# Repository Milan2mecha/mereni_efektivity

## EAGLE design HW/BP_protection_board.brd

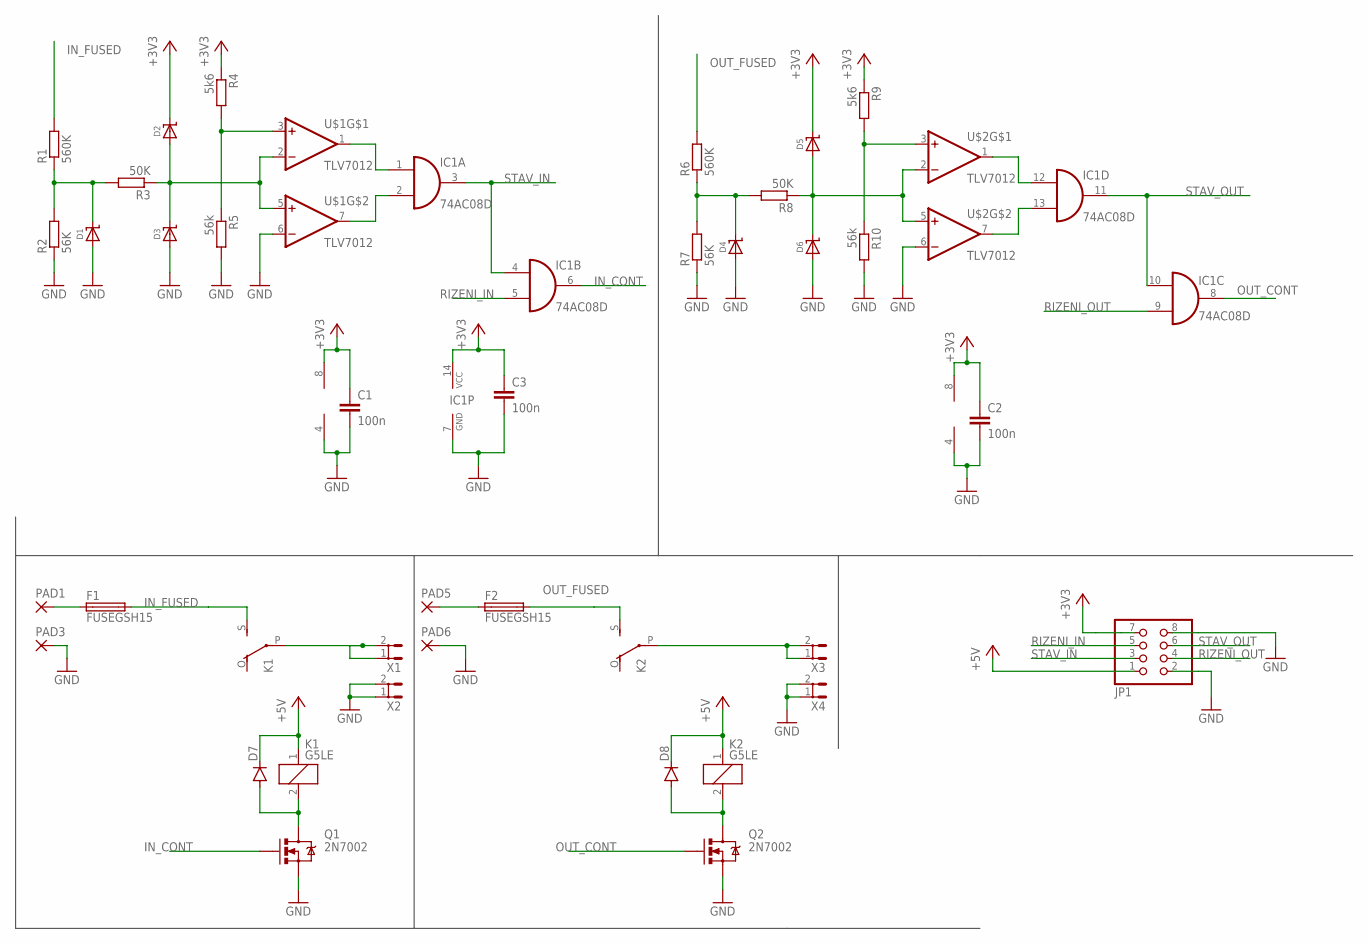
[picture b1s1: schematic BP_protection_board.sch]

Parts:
C1, C2, C3: 100n; C0805
D1, D2, D3, D4, D5, D6: DIODE-SCHOTTKYSOD-123; SOD-123
D7, D8: DIODE-MELF-MLL41; MELF-MLL41
F1, F2: FUSEGSH15; GSH15
IC1: 74AC08D; SO14
JP1: PINHD-2X4; 2X04
K1, K2: G5LE
PAD1, PAD3, PAD5, PAD6: 2,54/1,0
Q1, Q2: 2N7002; SOT323
R1, R6: 560K; R0805
R2, R7: 56K; R0805
R3, R8: 50K; R0805
R4, R9: 5k6; R0805
R5, R10: 56k; R0805
U$1, U$2: TLV7012; SOT-23-THIN
X1, X2, X3, X4: ST6,3

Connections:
+3V3: C1.1, C2.1, C3.1, D2.C, D5.C, IC1.14 (VCC), JP1.7, R4.1, R9.1, U$1.8 (V+), U$2.8 (V+)
+5V: D7.C, D8.C, JP1.1, K1.1, K2.1
GND: C1.2, C2.2, C3.2, D1.A, D3.A, D4.A, D6.A, IC1.7 (GND), JP1.2, JP1.8, PAD3.1, PAD6.1, Q1.2 (S), Q2.2 (S), R2.1, R5.2, R7.1, R10.2, U$1.4 (V-), U$1.6 (-IN), U$2.4 (V-), U$2.6 (-IN), X2.1, X2.2, X4.1, X4.2
IN_CONT: IC1.6 (O), Q1.1 (G)
IN_FUSED: F1.2, K1.S, R1.2
unnamed: D1.C, R1.1, R2.2, R3.2
unnamed: D2.A, D3.C, R3.1, U$1.2 (-IN), U$1.5 (+IN)
unnamed: R4.2, R5.1, U$1.3 (+IN)
unnamed: D4.C, R6.1, R7.2, R8.2
unnamed: F1.1, PAD1.1
unnamed: D5.A, D6.C, R8.1, U$2.2 (-IN), U$2.5 (+IN)
unnamed: R9.2, R10.1, U$2.3 (+IN)
unnamed: K1.P, X1.1, X1.2
unnamed: K2.P, X3.1, X3.2
unnamed: D8.A, K2.2, Q2.3 (D)
unnamed: D7.A, K1.2, Q1.3 (D)
unnamed: IC1.1 (I0), U$1.1 (OUT)
unnamed: IC1.2 (I1), U$1.7 (OUT)
unnamed: F2.1, PAD5.1
unnamed: IC1.12 (I0), U$2.1 (OUT)
unnamed: IC1.13 (I1), U$2.7 (OUT)
OUT_CONT: IC1.8 (O), Q2.1 (G)
OUT_FUSED: F2.2, K2.S, R6.2
RIZENI_IN: IC1.5 (I1), JP1.5
RIZENI_OUT: IC1.9 (I0), JP1.4
STAV_IN: IC1.3 (O), IC1.4 (I0), JP1.3
STAV_OUT: IC1.10 (I1), IC1.11 (O), JP1.6

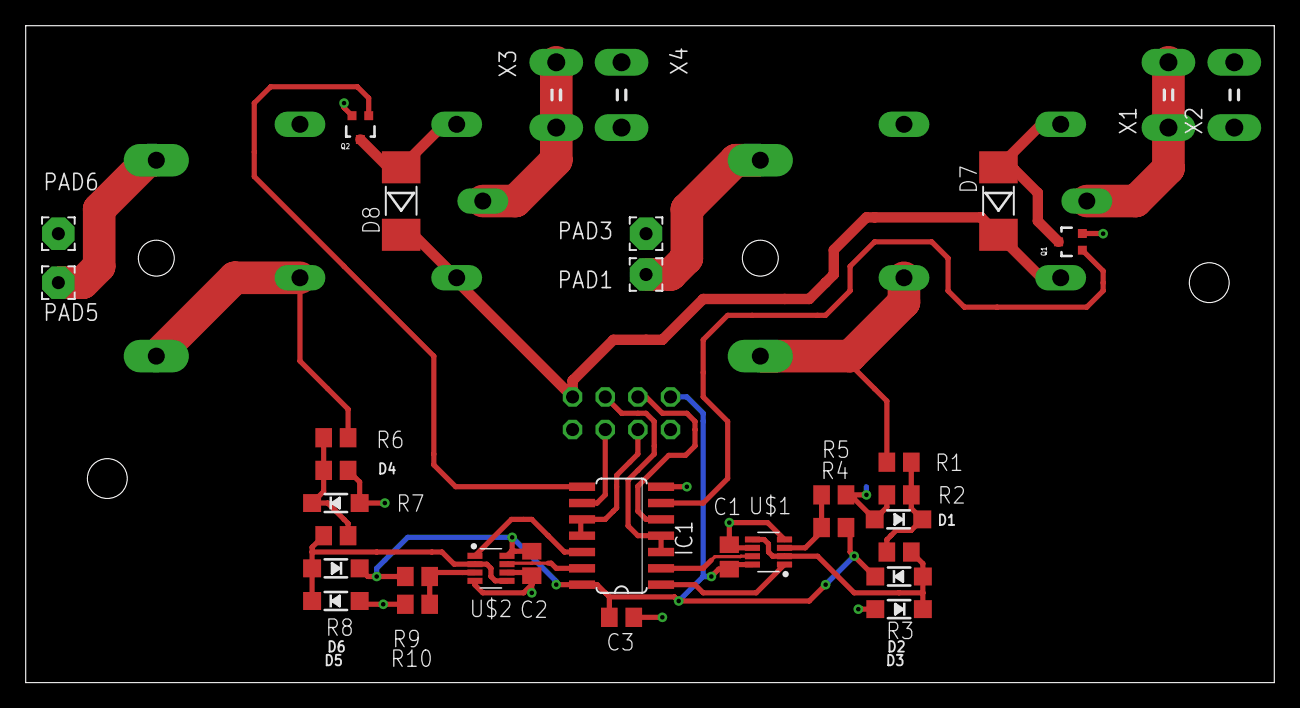
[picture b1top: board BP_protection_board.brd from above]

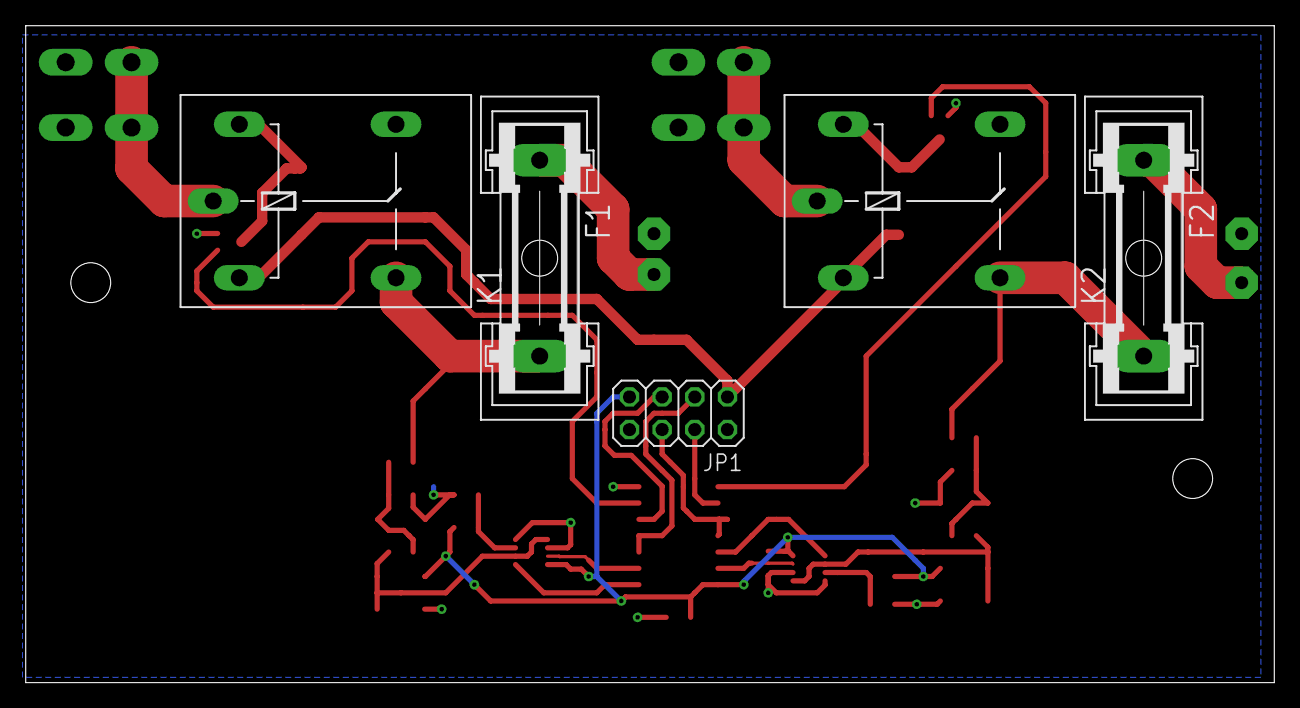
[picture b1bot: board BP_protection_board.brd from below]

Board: 2 copper layers, 97.1 x 51.1 mm, 39 parts (5 on the bottom side), 27 nets.

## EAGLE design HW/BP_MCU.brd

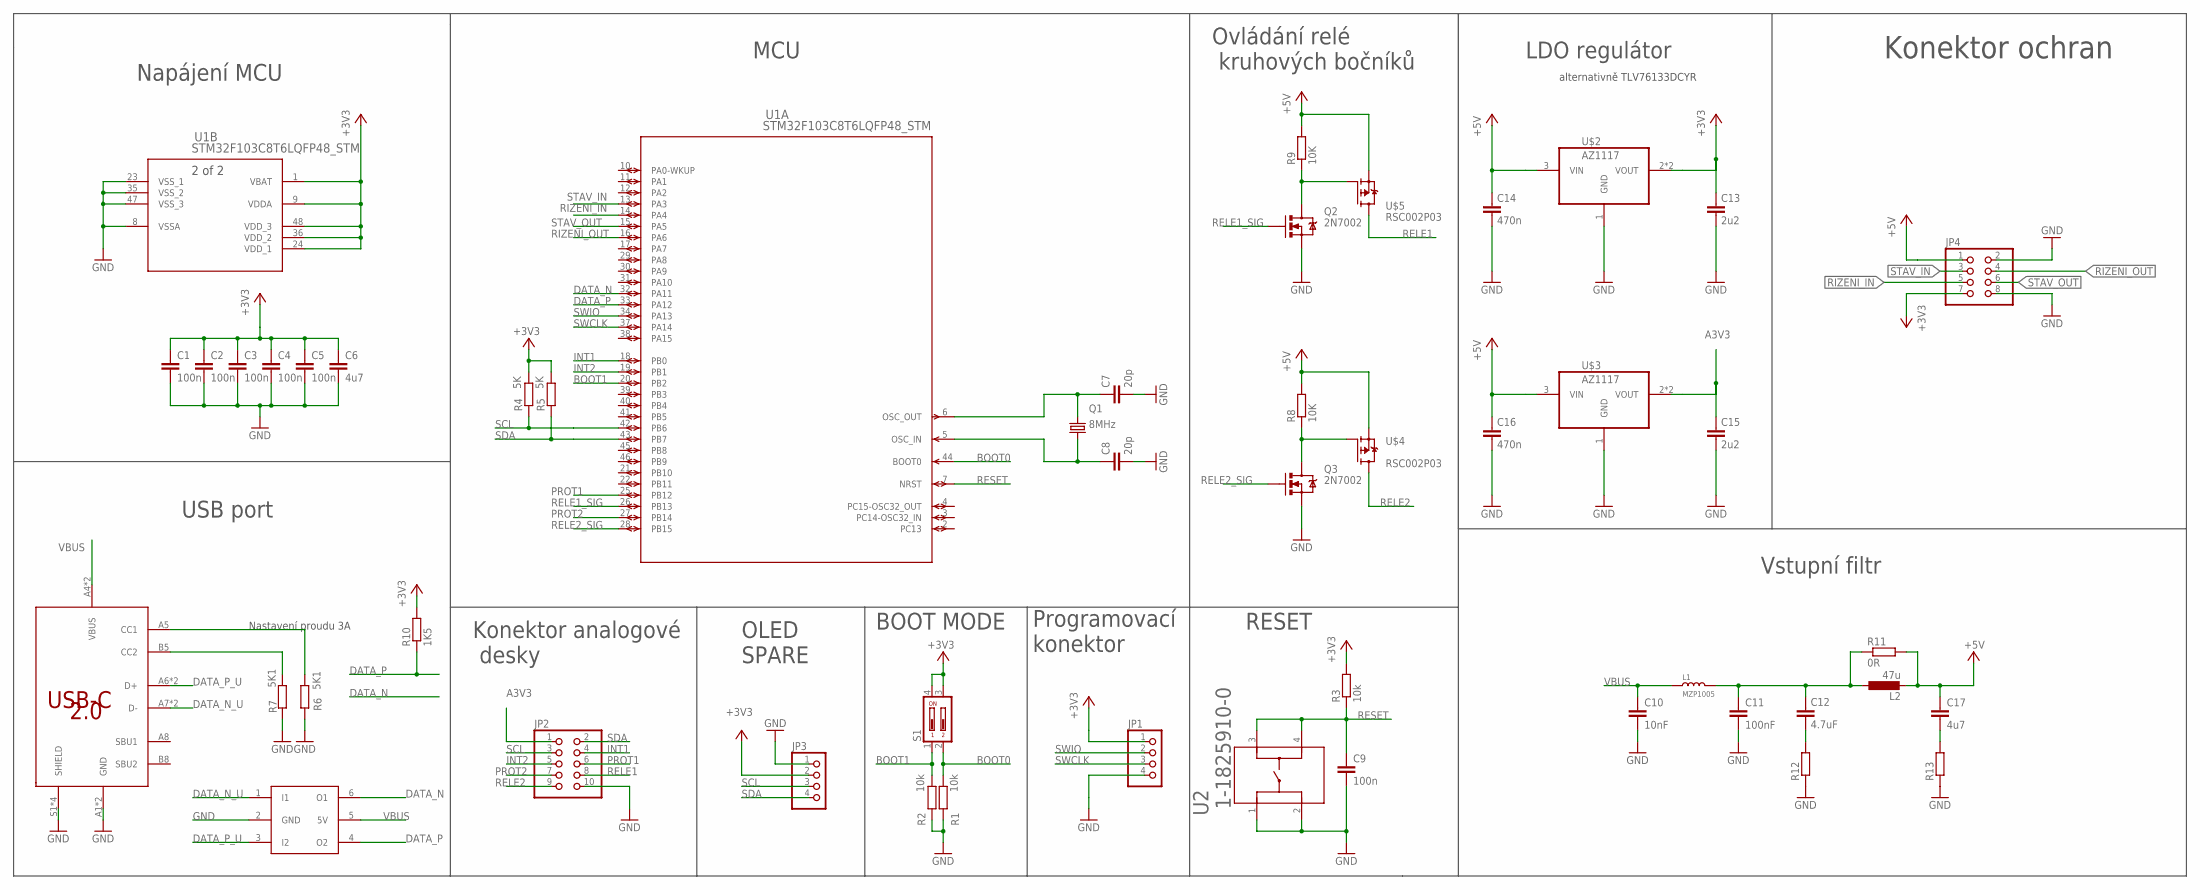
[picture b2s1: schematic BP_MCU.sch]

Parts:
C1, C2, C3, C4, C5, C9: 100n; C0805
C6, C17: 4u7; C0805
C7, C8: 20p; C0805
C10: 10nF; C0805
C11: 100nF; C0805
C12: 4.7uF; C0805
C13, C15: 2u2; C0805
C14, C16: 470n; C0805
JP1, JP3: PINHD-1X4; 1X04
JP2: PINHD-2X5; 2X05
JP4: PINHD-2X4; 2X04
L1: MZP1005; INDUCTOR_L0402
L2: 47u; AMRM001
Q1: 8MHz; HC49UP
Q2, Q3: 2N7002; SOT323
R1, R2, R3: 10k; R0805
R4, R5: 5K; R0805
R6, R7: 5K1; R0805
R8, R9: 10K; R0805
R10: 1K5; R0805
R11: 0R; R0805
R12, R13: R-EU_R0805; R0805
S1: SD4-02
U1: STM32F103C8T6LQFP48_STM; LQFP48_STM
U2: 1-1825910-0; SWITCH_1-1825910-0
U$1: 217179-0001-USB-C; TYPEC16
U$2, U$3: AZ1117; SOT230P700X180-4N
U$4, U$5: RSC002P03; SOT95
U$6: USBLC6-2; SOT23-6L

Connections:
+3V3: C1.1, C2.1, C3.1, C4.1, C5.1, C6.1, C13.1, JP1.1, JP3.2, JP4.7, R3.2, R4.2, R5.2, R10.2, S1.3, S1.4, U1.1 (VBAT), U1.9 (VDDA), U1.24 (VDD_1), U1.36 (VDD_2), U1.48 (VDD_3), U$2.2 (VOUT), U$2.4 (VOUT)
+5V: C14.1, C16.1, C17.1, JP4.1, L2.P$2 (2), R8.2, R9.2, R11.2, U$2.3 (VIN), U$3.3 (VIN), U$4.1 (S), U$5.1 (S)
A3V3: C15.1, JP2.1, U$3.2 (VOUT), U$3.4 (VOUT)
BOOT0: R1.2, S1.2, U1.44 (BOOT0)
BOOT1: R2.2, S1.1, U1.20 (PB2)
DATA_N: U1.32 (PA11), U$6.6 (O1)
DATA_N_U: U$1.A7 (D-), U$1.B7 (D-), U$6.1 (I1)
DATA_P: R10.1, U1.33 (PA12), U$6.4 (O2)
DATA_P_U: U$1.A6 (D+), U$1.B6 (D+), U$6.3 (I2)
GND: C1.2, C2.2, C3.2, C4.2, C5.2, C6.2, C7.2, C8.2, C9.2, C10.2, C11.2, C13.2, C14.2, C15.2, C16.2, JP1.4, JP2.10, JP3.1, JP4.2, JP4.8, Q2.2 (S), Q3.2 (S), R1.1, R2.1, R6.2, R7.2, R12.1, R13.1, U1.8 (VSSA), U1.23 (VSS_1), U1.35 (VSS_2), U1.47 (VSS_3), U2.1, U2.2, U$1.A1 (GND), U$1.A12 (GND), U$1.S1 (SHIELD), U$1.S2 (SHIELD), U$1.S3 (SHIELD), U$1.S4 (SHIELD), U$2.1 (GND), U$3.1 (GND), U$6.2 (GND)
INT1: JP2.4, U1.18 (PB0)
INT2: JP2.5, U1.19 (PB1)
unnamed: Q2.3 (D), R9.1, U$5.2 (G)
unnamed: Q3.3 (D), R8.1, U$4.2 (G)
unnamed: R7.1, U$1.B5 (CC2)
unnamed: R6.1, U$1.A5 (CC1)
unnamed: C12.2, R12.2
unnamed: C11.1, C12.1, L1.2, L2.P$1 (1), R11.1
unnamed: C17.2, R13.2
OSC_N: C8.1, Q1.1, U1.5 (OSC_IN)
OSC_P: C7.1, Q1.2, U1.6 (OSC_OUT)
PROT1: JP2.6, U1.25 (PB12)
PROT2: JP2.7, U1.27 (PB14)
RELE1: JP2.8, U$5.3 (D)
RELE1_SIG: Q2.1 (G), U1.26 (PB13)
RELE2: JP2.9, U$4.3 (D)
RELE2_SIG: Q3.1 (G), U1.28 (PB15)
RESET: C9.1, R3.1, U1.7 (NRST), U2.3, U2.4
RIZENI_IN: JP4.5, U1.14 (PA4)
RIZENI_OUT: JP4.4, U1.16 (PA6)
SCL: JP2.3, JP3.3, R4.1, U1.42 (PB6)
SDA: JP2.2, JP3.4, R5.1, U1.43 (PB7)
STAV_IN: JP4.3, U1.13 (PA3)
STAV_OUT: JP4.6, U1.15 (PA5)
SWCLK: JP1.3, U1.37 (PA14)
SWIO: JP1.2, U1.34 (PA13)
VBUS: C10.1, L1.1, U$1.A4 (VBUS), U$1.A9 (VBUS), U$6.5 (5V)

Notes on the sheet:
Nastavení proudu 3A
LDO regulátor
alternativně TLV76133DCYR
Napájení MCU
USB port
MCU
Konektor analogové desky
OLED SPARE
BOOT MODE
Programovací konektor
RESET
Ovládání relé kruhových bočníků
Vstupní filtr
Konektor ochran

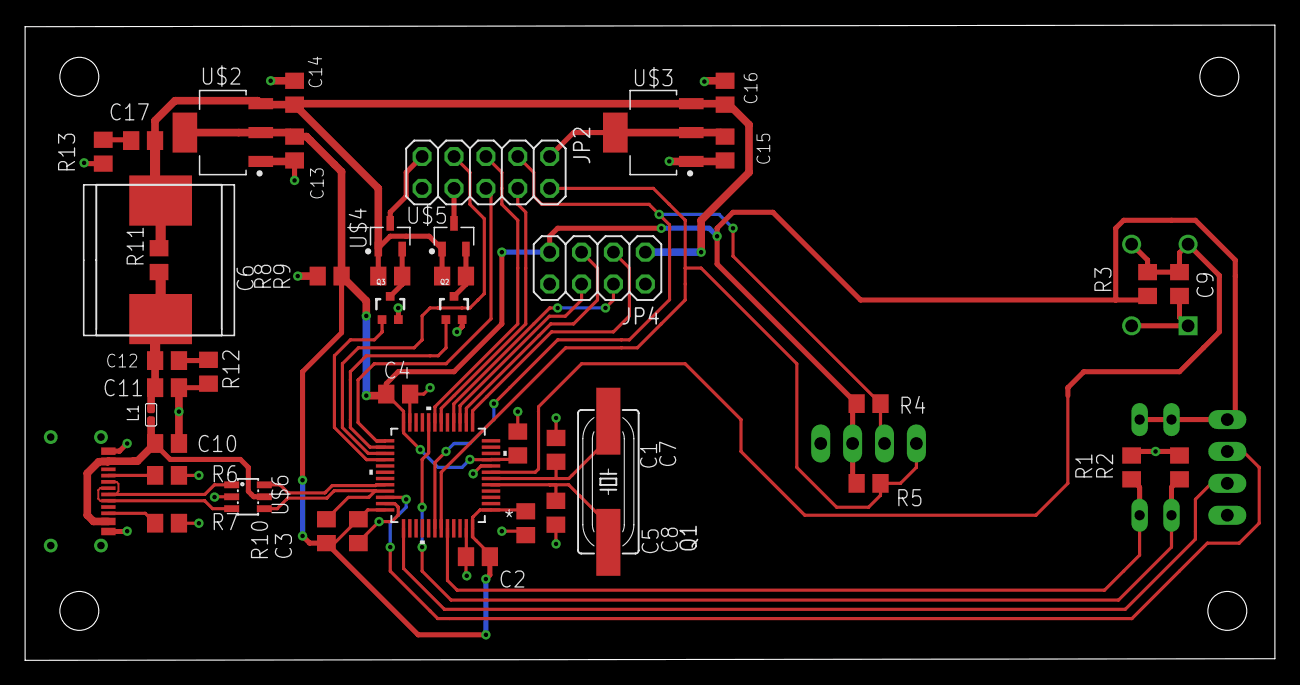
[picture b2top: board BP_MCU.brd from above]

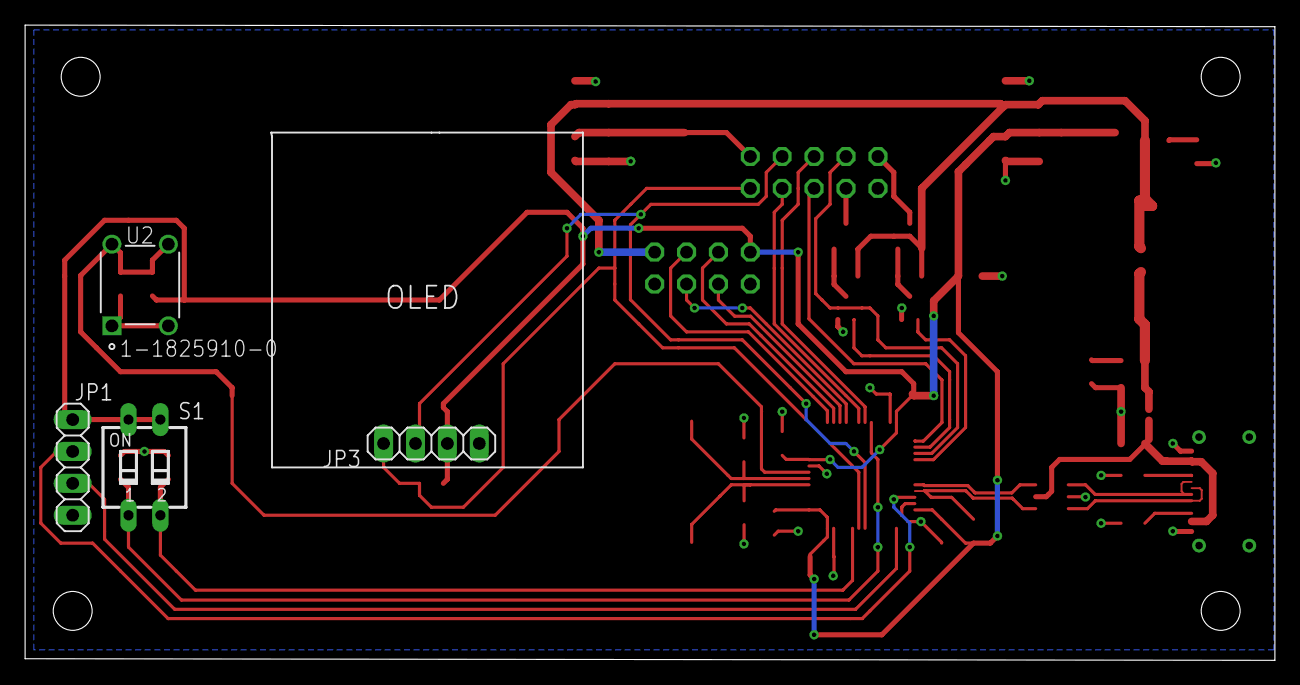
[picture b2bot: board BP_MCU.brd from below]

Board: 2 copper layers, 99.5 x 50.6 mm, 48 parts (4 on the bottom side), 37 nets.

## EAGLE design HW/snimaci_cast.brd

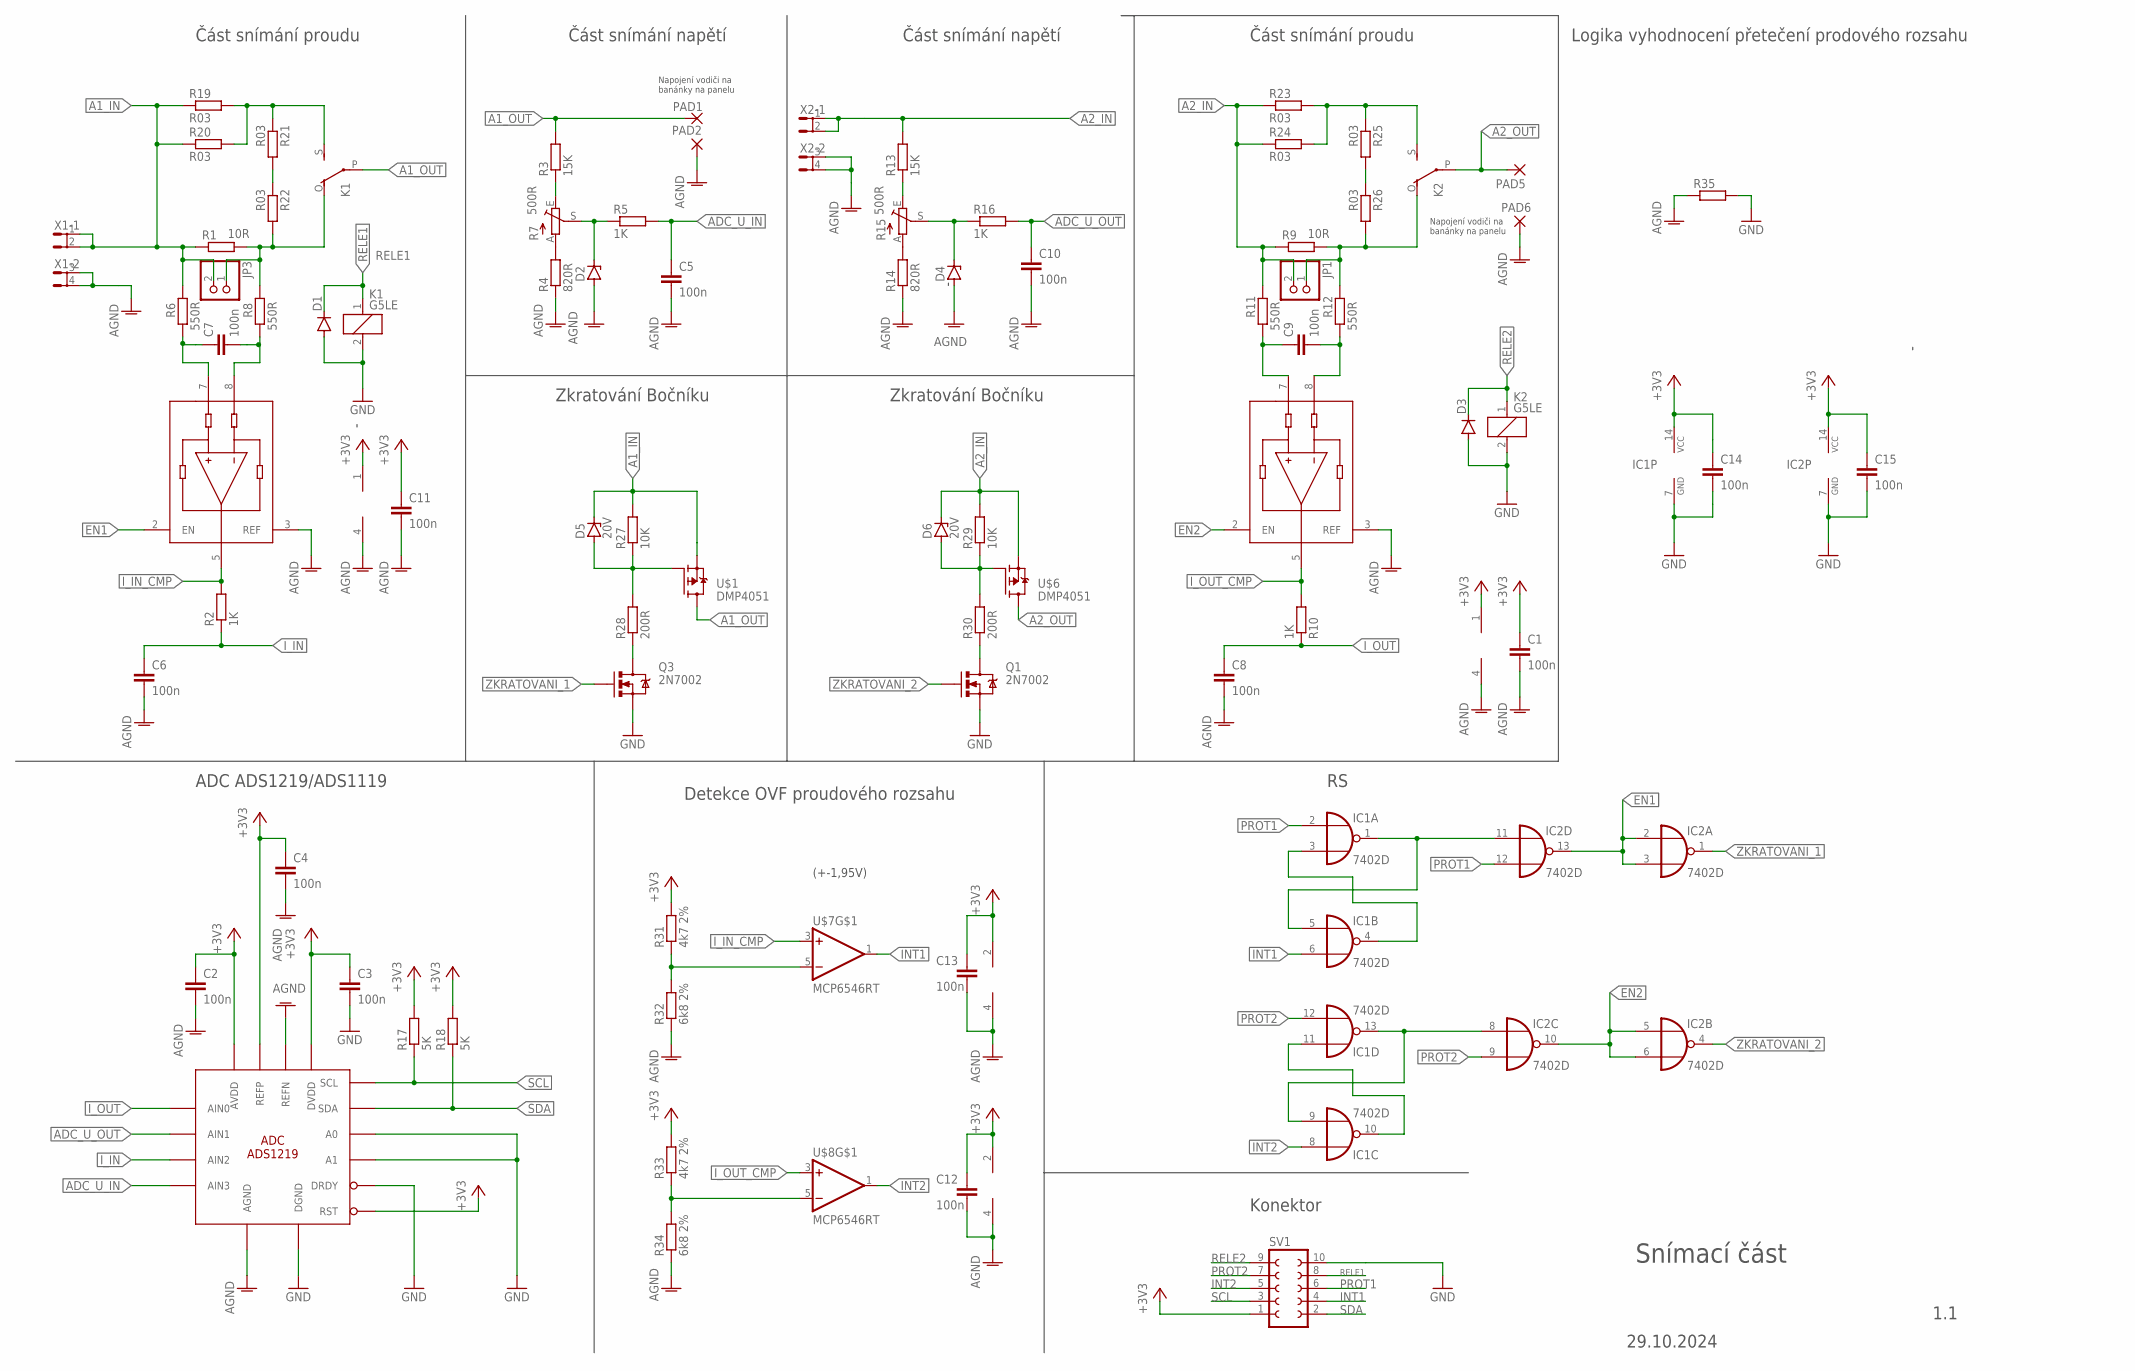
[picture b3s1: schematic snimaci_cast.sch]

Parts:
C1, C2, C3, C4, C5, C6, C7, C8, C9, C10, C11, C12, C13, C14, C15: 100n; C0805
D1, D3: DIODE-MELF-MLL41; MELF-MLL41
D2, D4: ZENER-DIODESOD80C; SOD80C
D5, D6: 20V; SMB
IC1, IC2: 7402D; SO14
JP1, JP3: PINHD-1X2; 1X02
K1, K2: G5LE
PAD1, PAD2, PAD5, PAD6: 2,15/1,0
Q1, Q3: 2N7002; SOT323
R1, R9: 10R; R1206
R2, R5, R10, R16: 1K; R0805
R3, R13: 15K; R0805
R4, R14: 820R; R0805
R6, R8, R11, R12: 550R; R0805
R7, R15: 500R; PT-10
R17, R18: 5K; R0805
R19, R20, R21, R22, R23, R24, R25, R26: R03; R1206
R27, R29: 10K; R0805
R28, R30: 200R; R0805
R31, R33: 4k7 2%; R0805
R32, R34: 6k8 2%; R0805
R35: R-EU_R0805; R0805
SV1: FE05-2
U$1, U$6: DMP4051; TO252
U$2: ADS1219; TSSOP16
U$4, U$5: INA190; SOT-23-THIN
U$7, U$8: MCP6546RT; SOT23-5
X1, X2: SH5-2

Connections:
+3V3: C1.1, C2.1, C3.1, C4.1, C11.1, C12.1, C13.1, C14.1, C15.1, IC1.14 (VCC), IC2.14 (VCC), R17.2, R18.2, R31.2, R33.2, SV1.1, U$2.3 (RST), U$2.9 (REFP), U$2.12 (AVDD), U$2.13 (DVDD), U$4.1 (V+), U$5.1 (V+), U$7.2 (V+), U$8.2 (V+)
A1_IN: D5.C, JP3.2, R1.1, R6.2, R19.1, R20.1, R27.2, U$1.2 (S), X1.1, X1.2
A1_OUT: K1.P, PAD1.1, R3.2, U$1.3 (D)
A2_IN: D6.C, JP1.2, R9.1, R11.2, R13.2, R23.1, R24.1, R29.2, U$6.2 (S), X2.1, X2.2
A2_OUT: K2.P, PAD5.1, U$6.3 (D)
ADC_U_IN: C5.1, R5.2, U$2.6 (AIN3)
ADC_U_OUT: C10.1, R16.2, U$2.10 (AIN1)
AGND: C1.2, C2.2, C4.2, C5.2, C6.2, C8.2, C10.2, C11.2, C12.2, C13.2, D2.A, D4.A, PAD2.1, PAD6.1, R4.1, R14.1, R32.1, R34.1, R35.1, U$2.5 (AGND), U$2.8 (REFN), U$4.3 (REF), U$4.4 (V-), U$5.3 (REF), U$5.4 (V-), U$7.4 (V-), U$8.4 (V-), X1.3 (1), X1.4 (2), X2.3 (1), X2.4 (2)
EN1: IC2.2 (I0), IC2.3 (I1), IC2.13 (O), U$4.2 (EN)
EN2: IC2.5 (I0), IC2.6 (I1), IC2.10 (O), U$5.2 (EN)
GND: C3.2, C14.2, C15.2, D1.A, D3.A, IC1.7 (GND), IC2.7 (GND), K1.2, K2.2, Q1.2 (S), Q3.2 (S), R35.2, SV1.10, U$2.1 (A0), U$2.2 (A1), U$2.4 (DGND), U$2.14 (DRDY)
INT1: IC1.6 (I1), SV1.4, U$7.1 (OUT)
INT2: IC1.8 (I0), SV1.5, U$8.1 (OUT)
I_IN: C6.1, R2.1, U$2.7 (AIN2)
I_IN_CMP: R2.2, U$4.5, U$7.3 (+IN)
I_OUT: C8.1, R10.1, U$2.11 (AIN0)
I_OUT_CMP: R10.2, U$5.5, U$8.3 (+IN)
unnamed: JP3.1, K1.O, R1.2, R8.2, R22.2
unnamed: R3.1, R7.E
unnamed: R4.2, R7.A
unnamed: D2.C, R5.1, R7.S
unnamed: JP1.1, K2.O, R9.2, R12.2, R26.2
unnamed: C7.2, R8.1, U$4.8 (-)
unnamed: D5.A, R27.1, R28.2, U$1.1 (G)
unnamed: R31.1, R32.2, U$7.5 (-IN)
unnamed: Q3.3 (D), R28.1
unnamed: D6.A, R29.1, R30.2, U$6.1 (G)
unnamed: R13.1, R15.E
unnamed: R14.2, R15.A
unnamed: D4.C, R15.S, R16.1
unnamed: K1.S, R19.2, R20.2, R21.1
unnamed: Q1.3 (D), R30.1
unnamed: C7.1, R6.1, U$4.7 (+)
unnamed: R21.2, R22.1
unnamed: R33.1, R34.2, U$8.5 (-IN)
unnamed: K2.S, R23.2, R24.2, R25.1
unnamed: R25.2, R26.1
unnamed: IC1.3 (I1), IC1.4 (O)
unnamed: IC1.10 (O), IC1.11 (I0)
OUT_N: C9.1, R11.1, U$5.7 (+)
OUT_P: C9.2, R12.1, U$5.8 (-)
PROT1: IC1.2 (I0), IC2.12 (I1), SV1.6
PROT2: IC1.12 (I1), IC2.9 (I1), SV1.7
Q_1: IC1.1 (O), IC1.5 (I0), IC2.11 (I0)
Q_2: IC1.9 (I1), IC1.13 (O), IC2.8 (I0)
RELE1: D1.C, K1.1, SV1.8
RELE2: D3.C, K2.1, SV1.9
SCL: R17.1, SV1.3, U$2.16 (SCL)
SDA: R18.1, SV1.2, U$2.15 (SDA)
ZKRATOVANI_1: IC2.1 (O), Q3.1 (G)
ZKRATOVANI_2: IC2.4 (O), Q1.1 (G)

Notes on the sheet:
Část snímání proudu
Část snímání napětí
Napojení vodiči na banánky na panelu
Konektor
Detekce OVF proudového rozsahu
(+-1,95V)
Snímací část
29.10.2024
1.1
Zkratování Bočníku
Logika vyhodnocení přetečení prodového rozsahu
ADC ADS1219/ADS1119

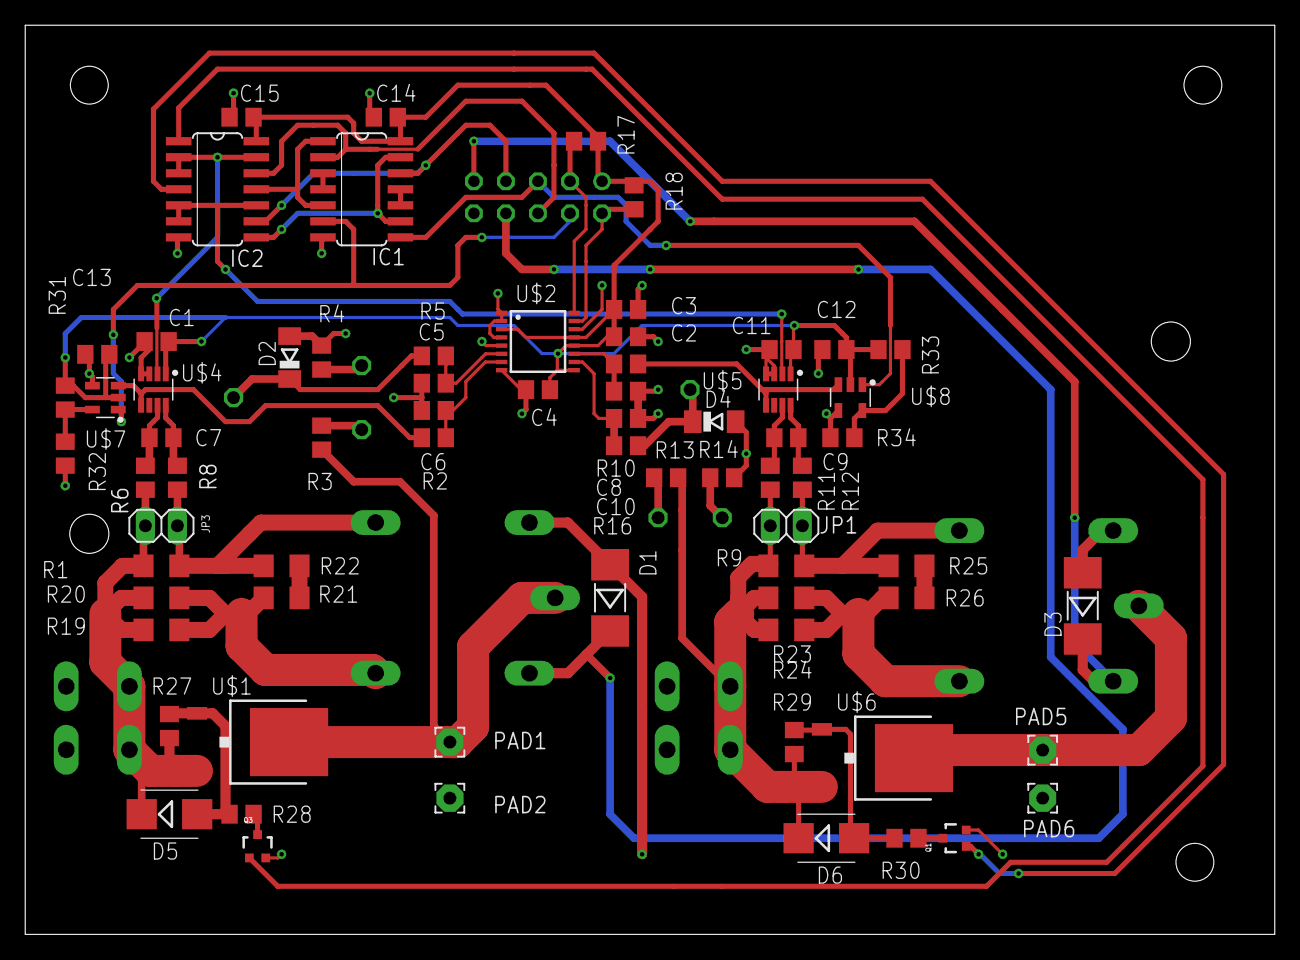
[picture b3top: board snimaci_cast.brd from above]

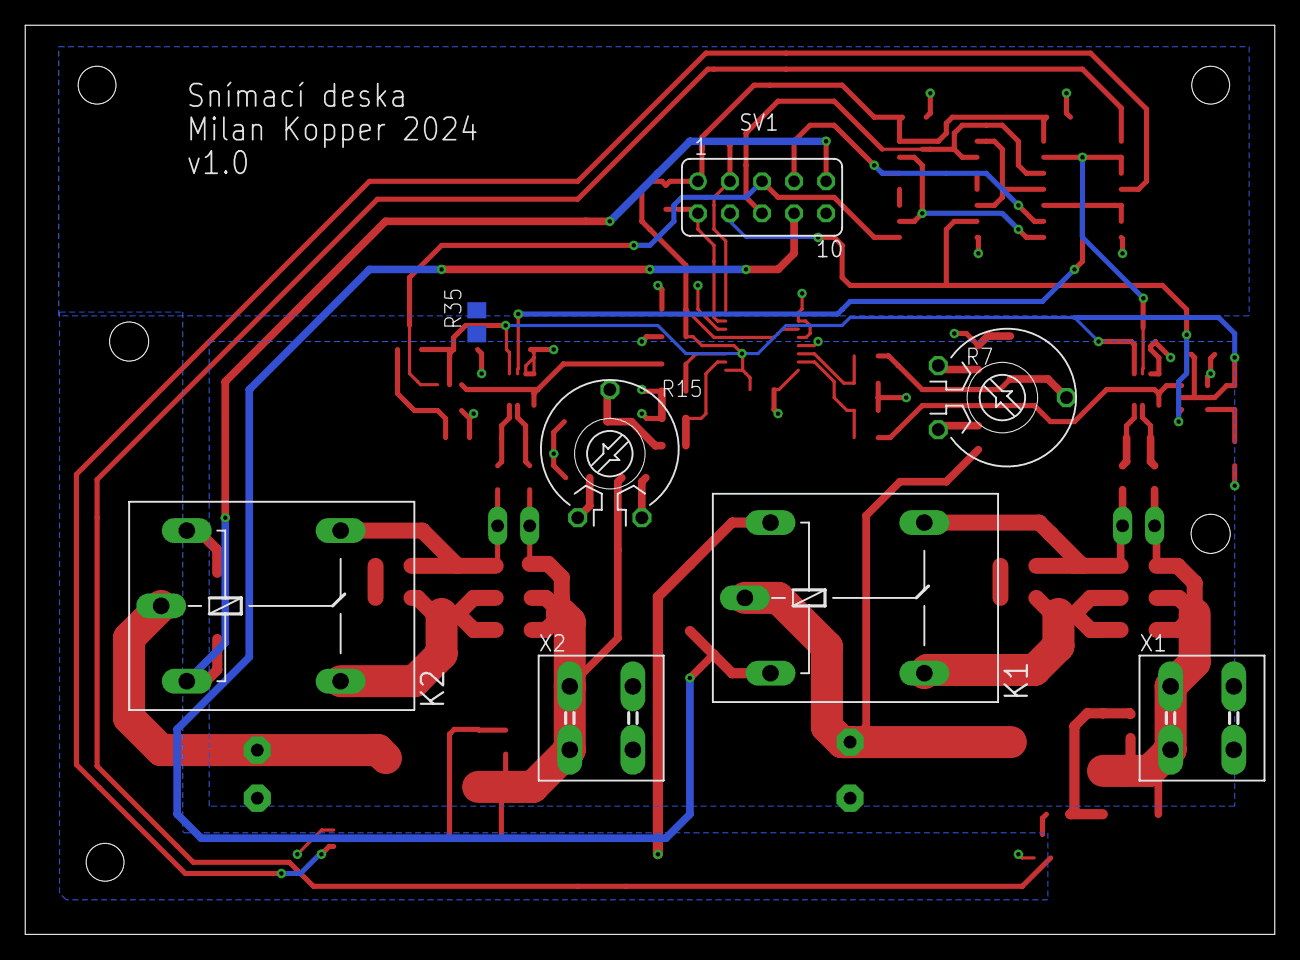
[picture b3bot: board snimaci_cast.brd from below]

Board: 2 copper layers, 99.0 x 72.1 mm, 78 parts (8 on the bottom side), 51 nets.

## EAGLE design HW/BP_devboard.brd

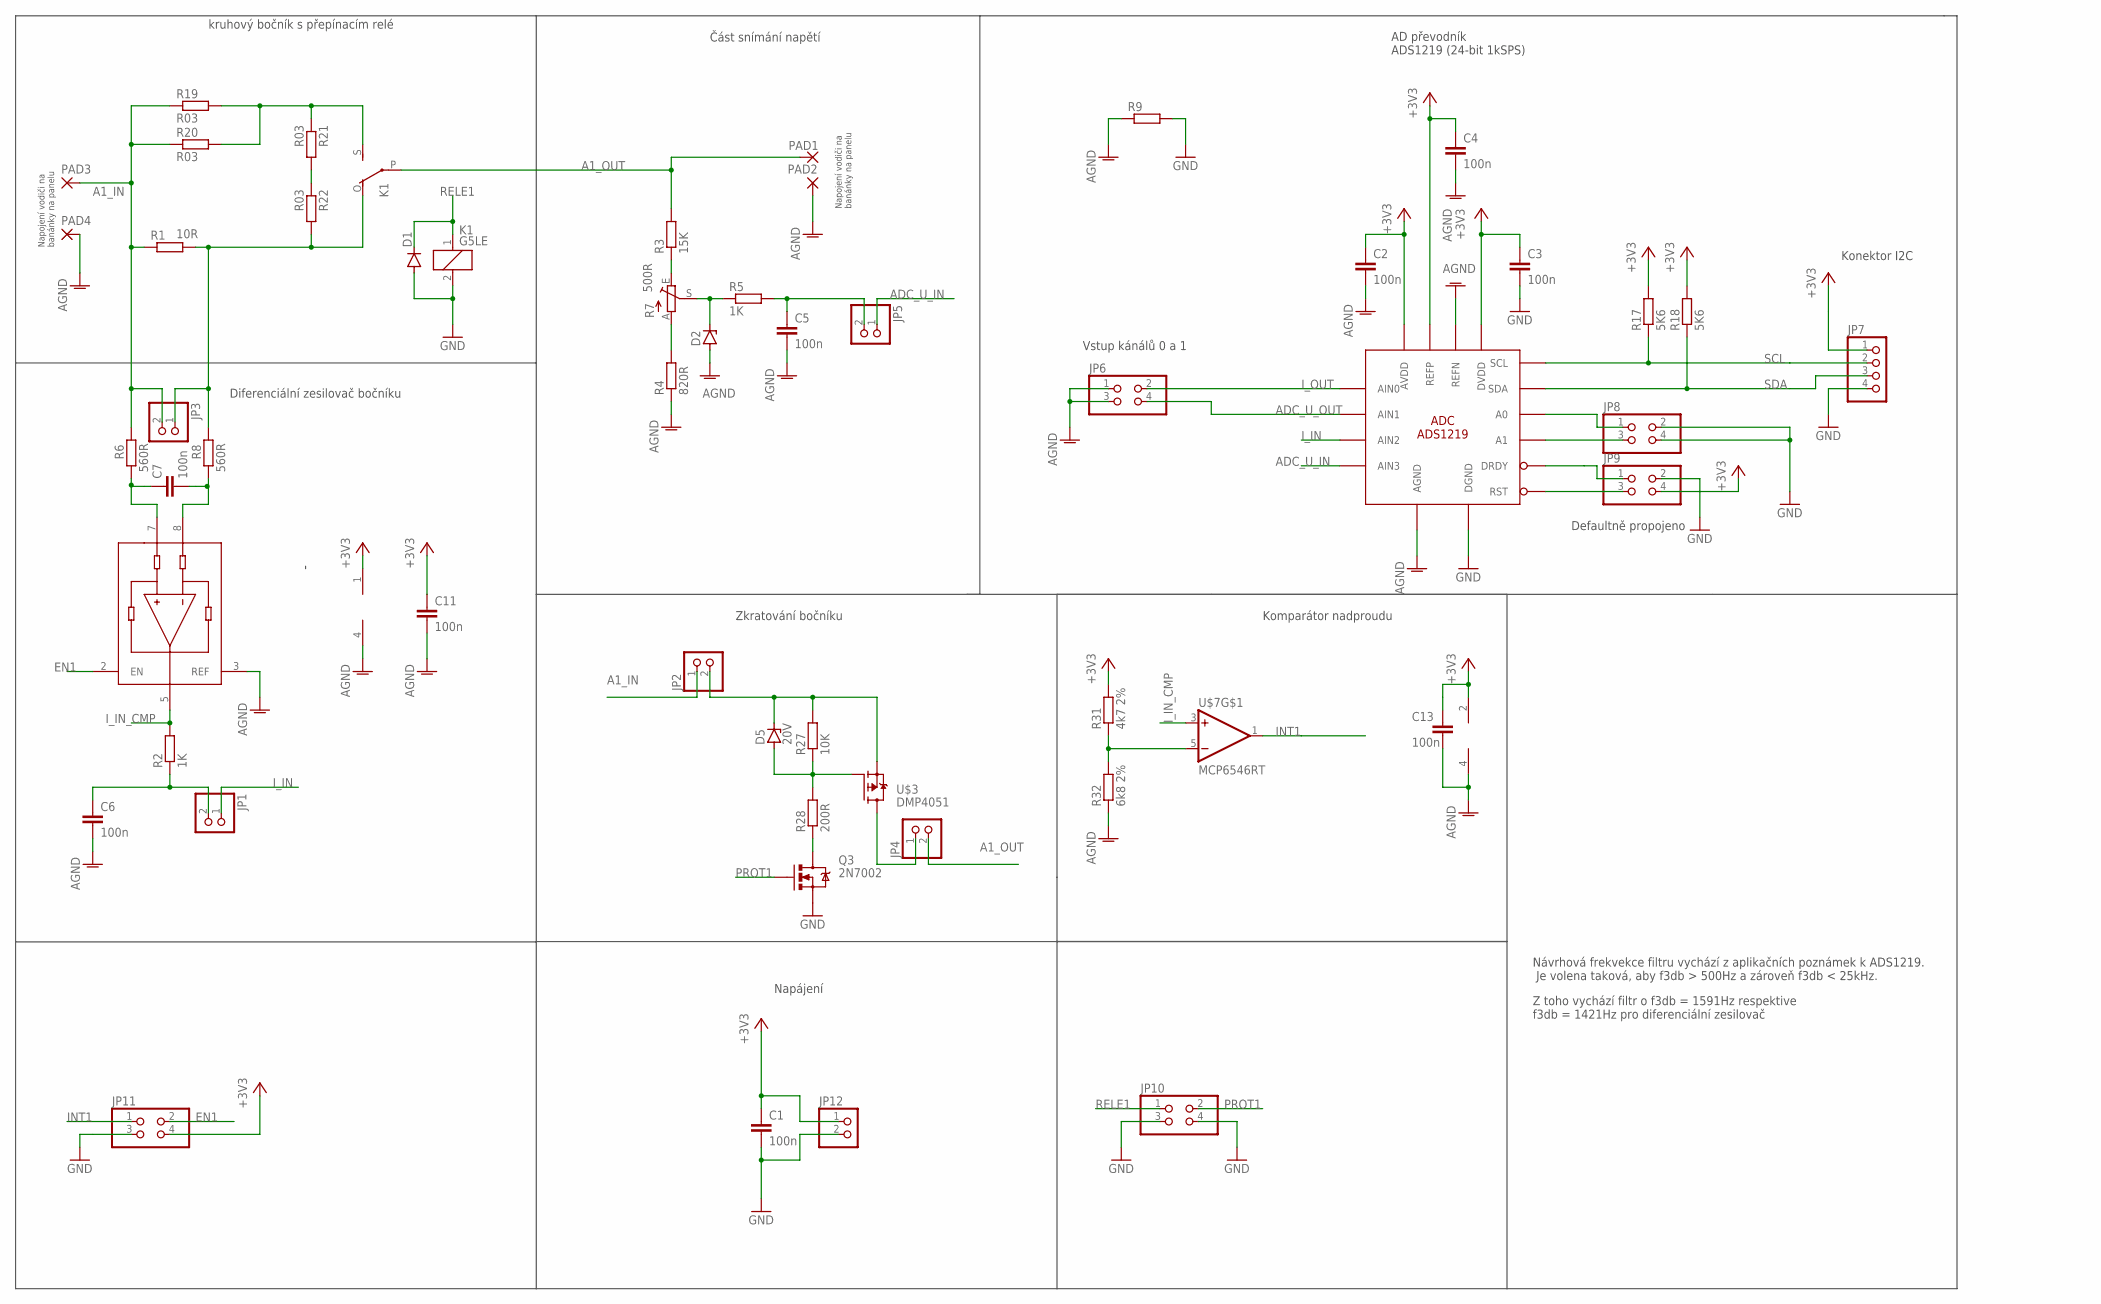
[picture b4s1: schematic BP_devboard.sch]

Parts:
C1, C2, C3, C4, C5, C6, C7, C11, C13: 100n; C0805
D1: DIODE-MELF-MLL41; MELF-MLL41
D2: ZENER-DIODESOD80C; SOD80C
D5: 20V; SMB
JP1, JP2, JP3, JP4, JP5, JP12: PINHD-1X2; 1X02
JP6, JP8, JP9, JP10, JP11: PINHD-2X2; 2X02
JP7: PINHD-1X4; 1X04
K1: G5LE
PAD1, PAD2, PAD3, PAD4: 2,15/1,0
Q3: 2N7002; SOT323
R1: 10R; R1206
R2, R5: 1K; R0805
R3: 15K; R0805
R4: 820R; R0805
R6, R8: 560R; R0805
R7: 500R; PT-10
R9: R-EU_R0805; R0805
R17, R18: 5K6; R0805
R19, R20, R21, R22: R03; R1206
R27: 10K; R0805
R28: 200R; R0805
R31: 4k7 2%; R0805
R32: 6k8 2%; R0805
U$2: ADS1219; TSSOP16
U$3: DMP4051; TO252
U$4: INA190; SOT-23-THIN
U$7: MCP6546RT; SOT23-5

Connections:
+3V3: C1.1, C2.1, C3.1, C4.1, C11.1, C13.1, JP7.1, JP9.4, JP11.4, JP12.1, R17.2, R18.2, R31.2, U$2.9 (REFP), U$2.12 (AVDD), U$2.13 (DVDD), U$4.1 (V+), U$7.2 (V+)
A1: JP8.3, U$2.2 (A1)
A1_IN: JP2.1, JP3.2, PAD3.1, R1.1, R6.2, R19.1, R20.1
A1_OUT: JP4.2, K1.P, PAD1.1, R3.2
ADC_U_IN: JP5.1, U$2.6 (AIN3)
ADC_U_OUT: JP6.4, U$2.10 (AIN1)
AGND: C2.2, C4.2, C5.2, C6.2, C11.2, C13.2, D2.A, JP6.1, JP6.3, PAD2.1, PAD4.1, R4.1, R9.1, R32.1, U$2.5 (AGND), U$2.8 (REFN), U$4.3 (REF), U$4.4 (V-), U$7.4 (V-)
EN1: JP11.2, U$4.2 (EN)
GND: C1.2, C3.2, D1.A, JP7.4, JP8.2, JP8.4, JP9.2, JP10.3, JP10.4, JP11.3, JP12.2, K1.2, Q3.2 (S), R9.2, U$2.4 (DGND)
INT1: JP11.1, U$7.1 (OUT)
I_IN: JP1.1, U$2.7 (AIN2)
I_IN_CMP: R2.2, U$4.5, U$7.3 (+IN)
I_OUT: JP6.2, U$2.11 (AIN0)
unnamed: JP3.1, K1.O, R1.2, R8.2, R22.2
unnamed: R3.1, R7.E
unnamed: R4.2, R7.A
unnamed: C6.1, JP1.2, R2.1
unnamed: D2.C, R5.1, R7.S
unnamed: JP4.1, U$3.3 (D)
unnamed: C7.2, R8.1, U$4.8 (-)
unnamed: D5.C, JP2.2, R27.2, U$3.2 (S)
unnamed: D5.A, R27.1, R28.2, U$3.1 (G)
unnamed: C5.1, JP5.2, R5.2
unnamed: Q3.3 (D), R28.1
unnamed: JP8.1, U$2.1 (A0)
unnamed: JP9.1, U$2.14 (DRDY)
unnamed: JP9.3, U$2.3 (RST)
unnamed: K1.S, R19.2, R20.2, R21.1
unnamed: R31.1, R32.2, U$7.5 (-IN)
unnamed: C7.1, R6.1, U$4.7 (+)
unnamed: R21.2, R22.1
PROT1: JP10.2, Q3.1 (G)
RELE1: D1.C, JP10.1, K1.1
SCL: JP7.2, R17.1, U$2.16 (SCL)
SDA: JP7.3, R18.1, U$2.15 (SDA)

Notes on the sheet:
Část snímání napětí
Napojení vodiči na banánky na panelu
Napájení
AD převodník ADS1219 (24-bit 1kSPS)
Konektor I2C
Defaultně propojeno
Vstup kánálů 0 a 1
Komparátor nadproudu
Zkratování bočníku
kruhový bočník s přepínacím relé
Diferenciální zesilovač bočníku
Návrhová frekvekce filtru vychází z aplikačních poznámek k ADS1219. Je volena taková, aby f3db > 500Hz a zároveň f3db < 25kHz.
Z toho vychází filtr o f3db = 1591Hz respektive f3db = 1421Hz pro diferenciální zesilovač

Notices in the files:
parts and their libraries:
COPYRIGHT: Copyright (C) 2024 Ultra Librarian. All rights reserved.
COPYRIGHT: Copyright (C) 2016 Accelerated Designs. All rights reserved
